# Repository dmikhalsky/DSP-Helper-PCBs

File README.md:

Комбо-плата для различных DSP проектов на базе чипов AD.
На плате:
1. DC-DC 3.3в конвертер питания на базе микросхемы ADP3338 (используется в evalution board на базе ADAU1467, ультра-низкий коэффициент шума) + повышающий импульсный DC-DC  5в/12в конвертер для питания ОУ (универсальное посадочное место, например Mornsun A0512S-1WR3)
2. DC-DC LDO +12В/-12В на базе tps7A3001/tps7A4901 для малошумного питания ОУ после импульсного DC-DC
3. 2 платы ОУ на базе OPA2134 и фильтра 2-го порядка с MFB-топологией*
4. 2 платы ОУ на базе линейного драйвера DRV602/603 и фильтра 2-го порядка с MFB-топологией*
5. конвертер TOSLINK -> SPDIF на базе PLR135T

ВАЖНО: на данный момент проверены и работают части (1), (3) и (5)

В в папке Simulation находится файл для программы TINA-TI для расчета параметров фильтра и подбора номиналов

В папке "Individual PCBs" находятся схемы каждой подплаты и отдельные KiCAD-файлы. Эти KiCAD не протестированы и могут содержать ошибки.

**Рабочим является только комбо-файл в корневой папке**

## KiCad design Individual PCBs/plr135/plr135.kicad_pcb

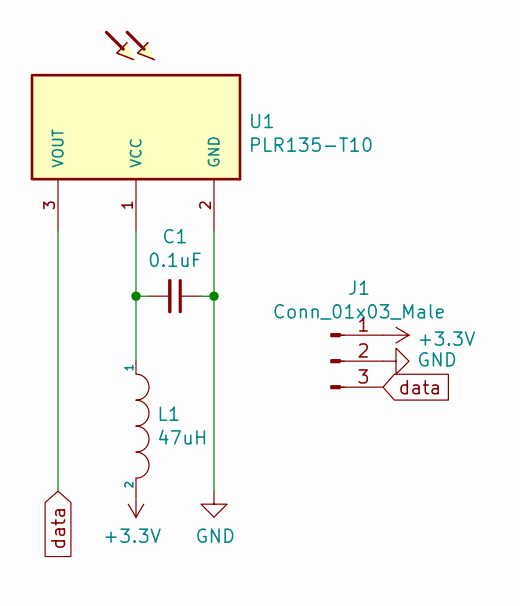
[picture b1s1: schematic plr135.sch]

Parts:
C1: 0.1uF; C_0805_HandSoldering
J1: Conn_01x03_Male; Pin_Header_Straight_1x03_Pitch2.54mm
L1: 47uH; L_0805_2012Metric_Pad1.05x1.20mm_HandSolder
U1: PLR135-T10; PLR135-T10_PLT133-T10W

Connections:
+3V3: J1.1, L1.2
GND: C1.1, J1.2, U1.2 (GND)
unnamed: C1.2, L1.1, U1.1 (VCC)
data: J1.3, U1.3 (VOUT)

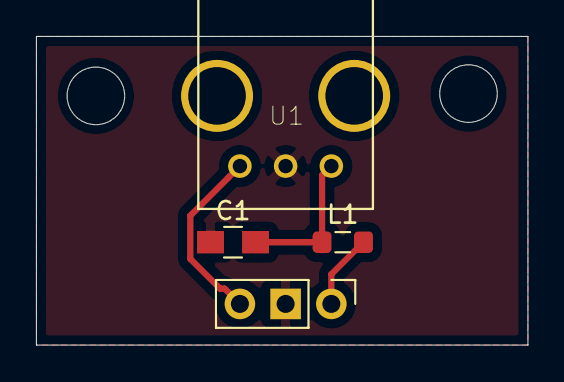
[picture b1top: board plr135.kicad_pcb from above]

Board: 2 copper layers, 27.3 x 17.1 mm, 4 parts (0 on the bottom side), 4 nets.

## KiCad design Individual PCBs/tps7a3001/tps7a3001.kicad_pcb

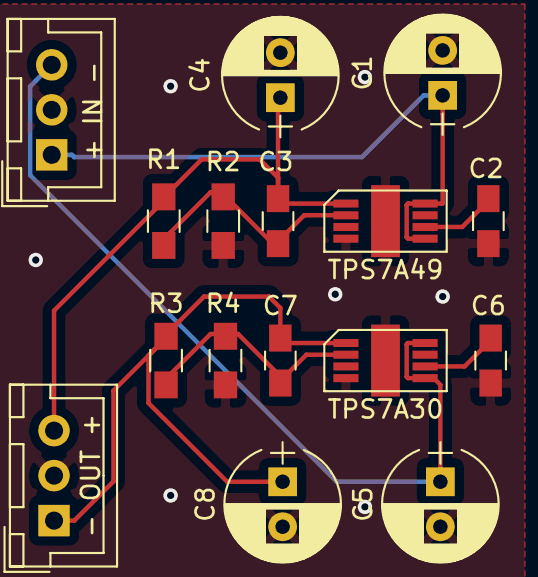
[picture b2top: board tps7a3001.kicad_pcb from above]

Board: 2 copper layers, 16 parts (0 on the bottom side), 9 nets.

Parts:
+ IN -: Input; JST_XH_B03B-XH-A_03x2.50mm_Straight
- OUT +: Output; JST_XH_B03B-XH-A_03x2.50mm_Straight
C1, C4, C5, C8: 10uf; CP_Radial_D6.3mm_P2.50mm
C2, C6: 10nf; C_0805_HandSoldering
C3, C7: 10uf; C_0805_HandSoldering
R1, R2, R3, R4: R_Small; R_0805_HandSoldering
TPS7A30, TPS7A49: TPS7Axxx; TPS7Axx

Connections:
+12V: + IN -.1, C1.1, TPS7A49.5, TPS7A49.8
-12V: + IN -.3, C5.1, TPS7A30.5, TPS7A30.8
GND: + IN -.2, - OUT +.2, C1.2, C2.2, C4.2, C5.2, C6.2, C8.2, R2.2, R4.2, TPS7A30.4, TPS7A49.4
unnamed: C2.1, TPS7A49.6
unnamed: C3.2, R1.2, R2.1, TPS7A49.2
unnamed: C6.1, TPS7A30.6
unnamed: C7.2, R3.2, R4.1, TPS7A30.2
VCC: - OUT +.3, C3.1, C4.1, R1.1, TPS7A49.1
VEE: - OUT +.1, C7.1, C8.1, R3.1, TPS7A30.1

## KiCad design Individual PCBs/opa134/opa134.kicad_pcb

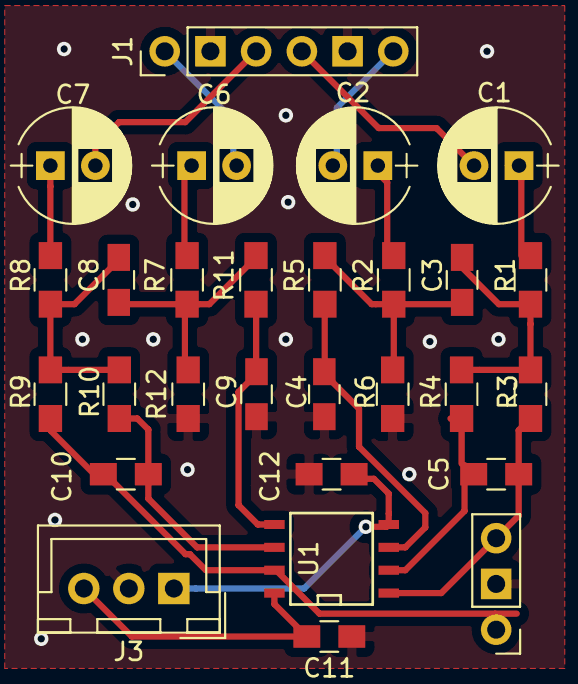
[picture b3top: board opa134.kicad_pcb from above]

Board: 2 copper layers, 28 parts (0 on the bottom side), 21 nets.

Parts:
C1, C2, C6, C7: 10uf; CP_Radial_D6.3mm_P2.50mm
C3, C4, C8, C9: 10uf; C_0805_HandSoldering
C5, C10: 220pf; C_0805_HandSoldering
C11, C12: C_Small; C_0805_HandSoldering
J1: Input; Pin_Header_Straight_1x06_Pitch2.54mm
J3: Power; JST_XH_B03B-XH-A_03x2.50mm_Straight
J4: Otput; Pin_Header_Straight_1x03_Pitch2.54mm
R1, R2, R3, R4, R5, R6, R7, R8, R10, R11, R12: 22k; R_0805_HandSoldering
R9: 5k6; R_0805_HandSoldering
U1: OPA2134; SOIC-8-N

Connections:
+12V: C11.2, J3.3, U1.8
-12V: C12.2, J3.1, U1.4
/AmpL+: C4.1, R5.1, U1.3
/AmpL-: C5.1, R4.1, U1.2
/AmpL_out: C5.2, J4.3, R3.2, U1.1
/AmpR+: C9.1, R11.2, U1.5
/AmpR-: C10.1, R10.2, U1.6
/AmpR_out: C10.2, J4.1, R9.2, U1.7
/INL+: C2.2, J1.6
/INL-: C1.2, J1.4
/INR+: C6.2, J1.1
/INR-: C7.2, J1.3
GND: C4.2, C9.2, C11.1, C12.1, J1.2, J1.5, J3.2, J4.2, R6.1, R12.1
unnamed: C1.1, R1.2
unnamed: C2.1, R2.2
unnamed: C3.1, R1.1, R3.1, R4.2
unnamed: C3.2, R2.1, R5.2, R6.2
unnamed: C6.1, R7.2
unnamed: C7.1, R8.2
unnamed: C8.1, R8.1, R9.1, R10.1
unnamed: C8.2, R7.1, R11.1, R12.2

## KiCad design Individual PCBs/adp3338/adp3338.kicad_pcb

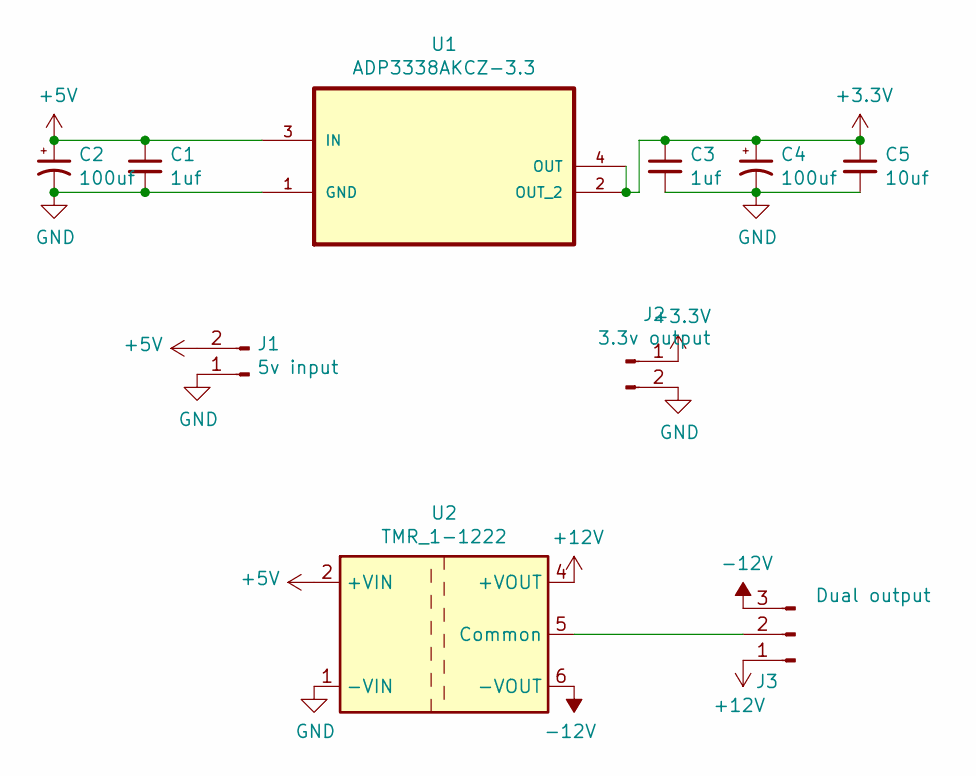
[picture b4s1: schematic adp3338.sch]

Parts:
C1, C3: 1uf; C_0805_HandSoldering
C2, C4: 100uf; CP_Radial_D6.3mm_P2.50mm
C5: 10uf; C_0805_HandSoldering
J1: 5v input; JST_XH_B02B-XH-A_02x2.50mm_Straight
J2: 3.3v output; JST_XH_B02B-XH-A_02x2.50mm_Straight
J3: Dual output; JST_XH_B03B-XH-A_03x2.50mm_Straight
U1: ADP3338AKCZ-3.3; SOT230P700X180-4N; MPN ADP3338AKCZ-3.3
U2: TMR_1-1222; TMH0512D

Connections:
+3V3: C3.1, C4.1, C5.1, J2.1, U1.2 (OUT_2), U1.4 (OUT)
+5V: C1.1, C2.1, J1.2, U1.3 (IN), U2.2 (+VIN)
+12V: J3.1, U2.4 (+VOUT)
-12V: J3.3, U2.6 (-VOUT)
GND: C1.2, C2.2, C3.2, C4.2, C5.2, J1.1, J2.2, U1.1 (GND), U2.1 (-VIN)
unnamed: J3.2, U2.5 (Common)

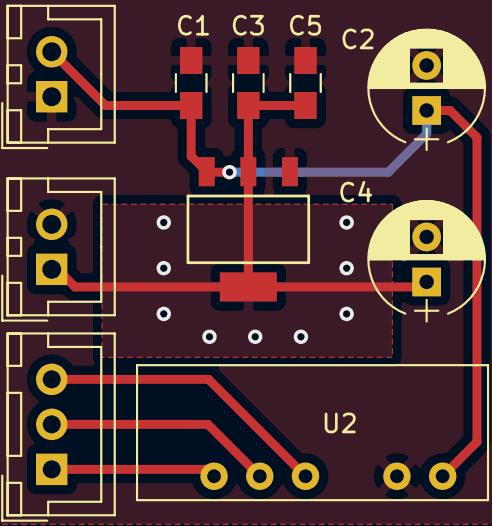
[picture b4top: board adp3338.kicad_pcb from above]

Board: 2 copper layers, 10 parts (0 on the bottom side), 6 nets.

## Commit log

2021-05-15 first full commit
